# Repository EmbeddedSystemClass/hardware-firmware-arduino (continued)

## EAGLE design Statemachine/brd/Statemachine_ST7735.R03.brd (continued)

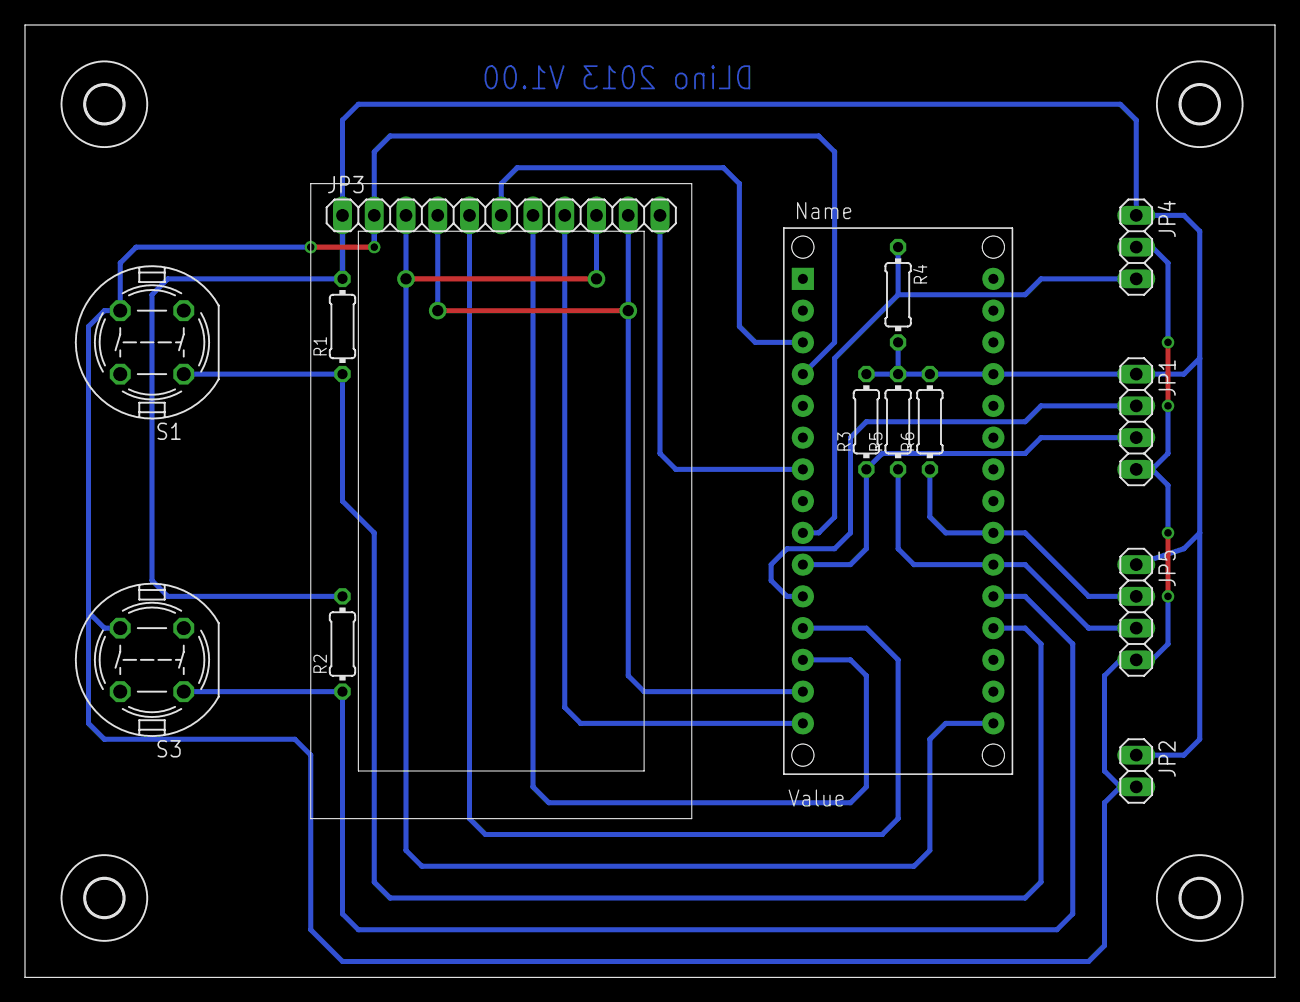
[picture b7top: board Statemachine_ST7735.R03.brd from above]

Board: 2 copper layers, 100.0 x 76.2 mm, 18 parts (0 on the bottom side), 16 nets.

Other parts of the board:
U$2, U$3, U$4, U$5: 3,0

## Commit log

2013-10-04 add ht-monitor
2013-10-14 add Datalogger 0815
2013-10-15 Statemachine
2013-10-15 implement simple logging
2013-10-15 =remove drewpoint
2013-10-16 implement software rtc
2013-10-17 String replace with PString
2013-10-18 remove error logging, new diplayText
2013-10-18 some corrections
2013-10-20 add button reading and debouncing, state switching, revise measureing
2013-10-21 add libraries
2013-10-21 edit time
2013-10-22 structures as bit fields
2013-10-22 solve errors
2013-10-23 add time events
2013-10-23 reset log menu
2013-10-25 pcb files
2013-10-27 add Noki_5110_Menu.txt
2013-10-28 add board
2013-10-28 add Statemachine
2013-10-28 change logging screen
2013-10-29 remove Nokia_5110_Menu.txt
2013-10-29 move pcb.zib > brd
2013-10-29 rename pcb.lib
2013-10-29 clean up
2013-10-29 cleanup
2013-11-02 edit strings
2013-11-03 edit date time
2013-11-03 cleanup, statemachine class, set date time
2013-11-04 organize code in classes
2013-11-04 rvised date time edit and display
2013-11-05 cleanup, edit options
2013-11-05 edit options revised
2013-11-05 add temperature chart
2013-11-06 revised charts
2013-11-06 edit temperature chart
2013-11-07 add measure.h
2013-11-07 revised measure
2013-11-07 remove
2013-11-07 adapt display
2013-11-07 rename Statemachine.ino
2013-11-08 add screens
2013-11-08 edit mainscreen
2013-11-10 edit menu screen
2013-11-11 edit date time screens
2013-11-12 edit options
2013-11-12 edit log settings
2013-11-13 clock test code with vba
2013-11-13 add clock
2013-11-13 edit main screen, display temperature
2013-11-14 remove clock vba
2013-11-14 add second temp sensor
2013-11-18 edit charts, logging
2013-11-18 edit logging
2013-11-19 board routed
2013-11-19 add sd card
2013-11-20 logging
2013-11-21 board rev 02
2013-12-02 add PTLogger
2013-12-06 begin test code
2013-12-12 add test
2013-12-12 simple analog read
2013-12-19 adapting lcd
2013-12-31 adapting rtc
2014-01-01 adapting menu
2014-01-06 error fixing
2014-01-11 date time edit revised
2014-01-13 Value Scree implemented.
2014-01-13 values screen revised
2014-05-09 Statemachine mit ST7783 TFT
2014-05-10 Tile Menu.
2014-05-11 Menu and editor changed.
2014-05-12 DateTime Screen implemented.
2014-05-12 resolved several errors.
2014-05-12 editors removed.
2014-05-12 add time editor.
2014-05-13 :clean up
2014-05-13 Testing Screen function pointers.
2014-05-13 clean up.
2014-05-13 solved screen handling.
2014-05-14 Clean up, add documentation.
2014-05-14 Temperatur measuerment fixed.
2014-05-14 change MainScreen layout, activate logger.
2014-05-14 add DS1821 documentation.
2014-05-15 chart design changed.
2014-05-15 chart fixed.
2014-05-15 clean up. DateTime set systime.
2014-05-17 Change font (unused chars removed), Files renamed.
2014-05-17 Show min, max, avg on MainScreen.
2014-05-17 LogSettings screen implemented.
2014-05-19 -add communication, -simple MFC application to set date and time.
2014-05-19 add forgotten communication.h.
2014-05-19 Rename Comunication.h to short form.
2014-05-20 Add CSharp Demo.
2014-05-20 Dokumentation.
2014-05-22 Add reporting.
2014-05-22 clean up, communication revised.
2014-05-23 Logger CSharp App revised, add petit lib.
2014-05-23 SD Test.
2014-05-23 Add Fat16
2014-05-24 file logging revised.
2014-05-25 Add new C# app with chart control.
2014-05-25 remove petit fs
2014-05-26 Add C# App with Net3.5
2014-05-27 UI revised, get files.
2014-05-27 change ui style.
2014-05-27 log files: directory und file transmitting.
2014-05-28 change ui
2014-05-28 remove resources.
2014-05-29 RTC: switch to DS1307.
    Rem: cut TFT reset pin and connect with pullup restistor to arduino reset pin.
2014-05-29 reset second.
2014-05-29 Temperature measurement: add DS1621.
2014-05-30 add second ds1621.
2014-05-30 add new rtc documentation.
2014-06-01 rtc adjust, add second temp chart.
2014-06-03 fix errors.
2014-06-03 net45 version.
2014-06-03 refreshing revised.
2014-06-03 receiving files test.
2014-06-06 add sandwich-logger pcb.
2014-06-13 new design.
2014-06-13 edit file export.
2014-06-13 fixing net45 version.
2014-06-18 Add progressbar.
2014-06-19 add TLC2543 demo.
2014-06-27 add docs invalidate temp gauge
2014-06-27 demo code
2014-06-28 add rv3049 doc
2014-06-29 Add logger with RTC RV3049 and ADC TLC2543
2014-07-01 add PT1000.xls
2014-07-01 add new Statemachine with ADC.
2014-07-03 fix SPI errors
2014-07-03 activate sensor 2
2014-07-04 -remove documentation, -add shield pcb
2014-07-05 add temperature table.
2014-07-05 add temperature sheet.
2014-07-05 remove temperature sheet.
2014-07-07 del.
2014-07-08 PCB: add reset note MainScreen: change gauges, try to optimize redrawing.
2014-07-08 errors fixed
2014-07-10 -cleanup, -add Statusbar.
2014-07-11 -errors fixed, -remove obsolet libs.
2014-07-12 cleanup.
2014-07-13 fix date time settings.
2014-07-13 set logging interval.
2014-07-14 VS2013 Project.
2014-07-14 VS2008 Project.
2014-07-14 replace definitions for example byte to uint8_t etc.
2014-07-14 remove LoggerNet35
2014-07-14 -events: set mode -com: ls
2014-07-15 some modifications.
2014-07-15 try to implement deleting files.
2014-07-31 LogEventManager: change interval evaluation.
2014-08-01 temperatur average of one houre.
2014-08-04 Errors fixed.
2014-08-06 temperature averaging removed.
2014-08-20 edit board.
2014-08-21 Remove Arduino text.
2014-09-16 remove some names.
2014-10-15 Voltage devider changed.
2014-10-15 Chip select signals changed.
2014-10-15 File transfer reworked.
2014-10-16 MiniTino hinzugefügt.
2014-10-16 Schema entfernt.
2014-10-17 Aktualisiert.
2014-10-24 Comunication reworked. MainScreen reworked.
2014-10-29 Change resistor packages.
2014-10-31 Start routing.
2014-12-23 Graph Test App.
2015-01-23 XModem File Transfer.
2015-01-23 modified App/CSharp/LoggerVS08/Logger/Logger/LogFilesTabPage.cs
2015-01-23 Progressbar reworked.
2015-01-28 -Charts reworked, -DateTime reworked.
2015-01-28 -XModem reworked, add array transfer, -Daylog transfer with XModem.
2015-01-28 Daylog revised.
2015-01-28 Daylog Chart revised.
2015-01-29 Chart.
2015-01-30 Logger App: Chart printing. Firmware: integer to char array, with neg. numbers.
2015-01-30 Print image.
2015-02-13 -Communication reworked, try async file request, -Charts reworked.
2015-02-16 fixing issues with neg. numbers.
2015-02-16 cancel transmission.
2015-02-19 Icons changed.
2015-02-20 App. Icons.
2015-02-20 Change Info.
2015-02-27 Printer selection.
2015-03-23 DDS with AD9850
2015-03-23 GLogger
2015-03-24 Project start.
2015-03-26 interval test changed.
2015-03-26 Brd.
2015-03-27 add Readme.txt
2015-03-27 Start.
2015-03-27 ADXL345 and SC-Card.
2015-03-27 SD Doc
2015-03-27 ST7833_DisplayDemo
2015-03-28 filename testing.
2015-03-30 switch to fat16.
2015-03-30 new sd lib.
2015-03-31 new Layout.
2015-04-10 Board changed.
2015-04-14 Rate changed.
2015-09-15 Thermometer Symbole beschriftet (IN, OUT).
2015-09-25 Update VS2013 Project.
2015-09-25 Find Arduinos.
2015-10-13 XModem removed. Data transfer with tags.
2015-10-16 libraries added.
2015-10-16 First tests.
2015-10-19 Testing.
2015-11-03 -File upload, -Webpage from SD Card.
2015-11-03 Directory function.
2015-11-04 File upload, download.
2015-11-06 Log interval settings.
2015-11-10 Ntp, Systemstate etc.
2015-11-10 Use DHCP.
2015-11-11 - Draw cursor in chart, - Interval changed.
2015-11-16 Fix error while file transfer.
2016-05-30 Import DCF.
2016-05-30 Import FT800_Test.
